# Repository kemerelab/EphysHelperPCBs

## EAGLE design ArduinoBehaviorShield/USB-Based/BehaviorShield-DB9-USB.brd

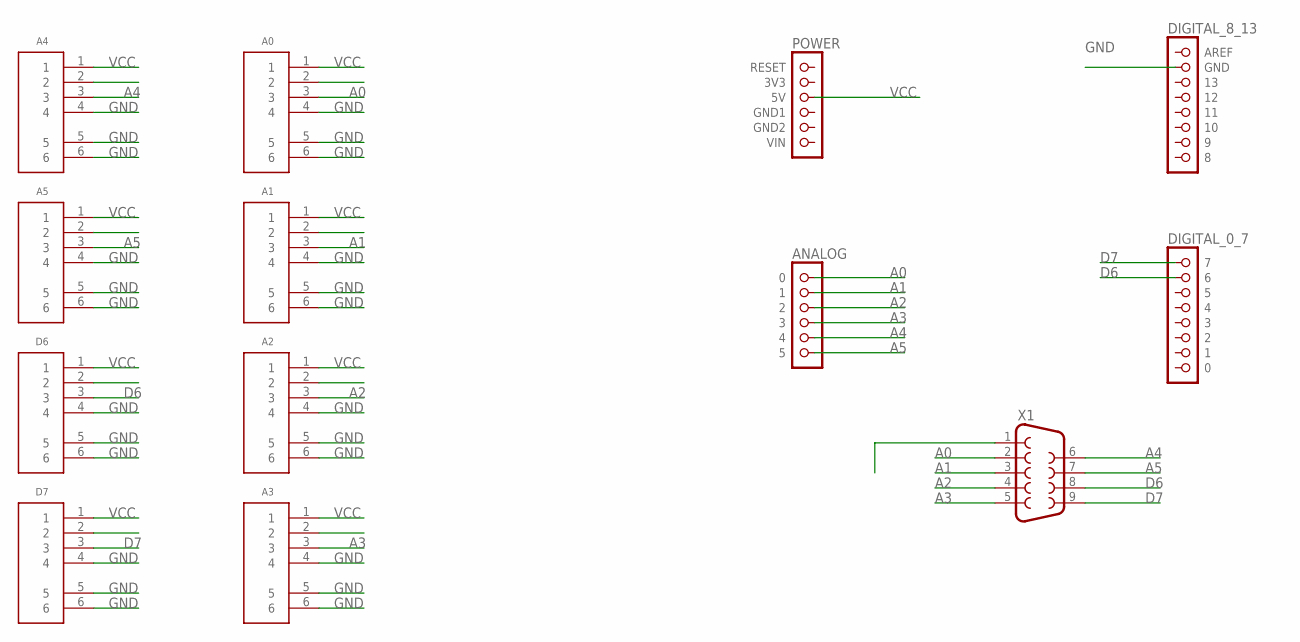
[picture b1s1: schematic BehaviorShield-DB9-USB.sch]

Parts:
A0, A1, A2, A3, A4, A5: USB-A-S-X-X-TH
D6, D7: USB-A-S-X-X-TH
U$1: POWER; 1X06
U$2: ANALOG; 1X06
U$3: DIGITAL_0_7; 1X08
U$4: DIGITAL_8_13; 1X08
X1: F09HP

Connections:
A0: A0.3, U$2.1 (0), X1.2
A1: A1.3, U$2.2 (1), X1.3
A2: A2.3, U$2.3 (2), X1.4
A3: A3.3, U$2.4 (3), X1.5
A4: A4.3, U$2.5 (4), X1.6
A5: A5.3, U$2.6 (5), X1.7
D6: D6.3, U$3.2 (6), X1.8
D7: D7.3, U$3.1 (7), X1.9
GND: A0.4, A0.5, A0.6, A1.4, A1.5, A1.6, A2.4, A2.5, A2.6, A3.4, A3.5, A3.6, A4.4, A4.5, A4.6, A5.4, A5.5, A5.6, D6.4, D6.5, D6.6, D7.4, D7.5, D7.6, U$4.2 (GND), X1.1
VCC: A0.1, A1.1, A2.1, A3.1, A4.1, A5.1, D6.1, D7.1, U$1.3 (5V)

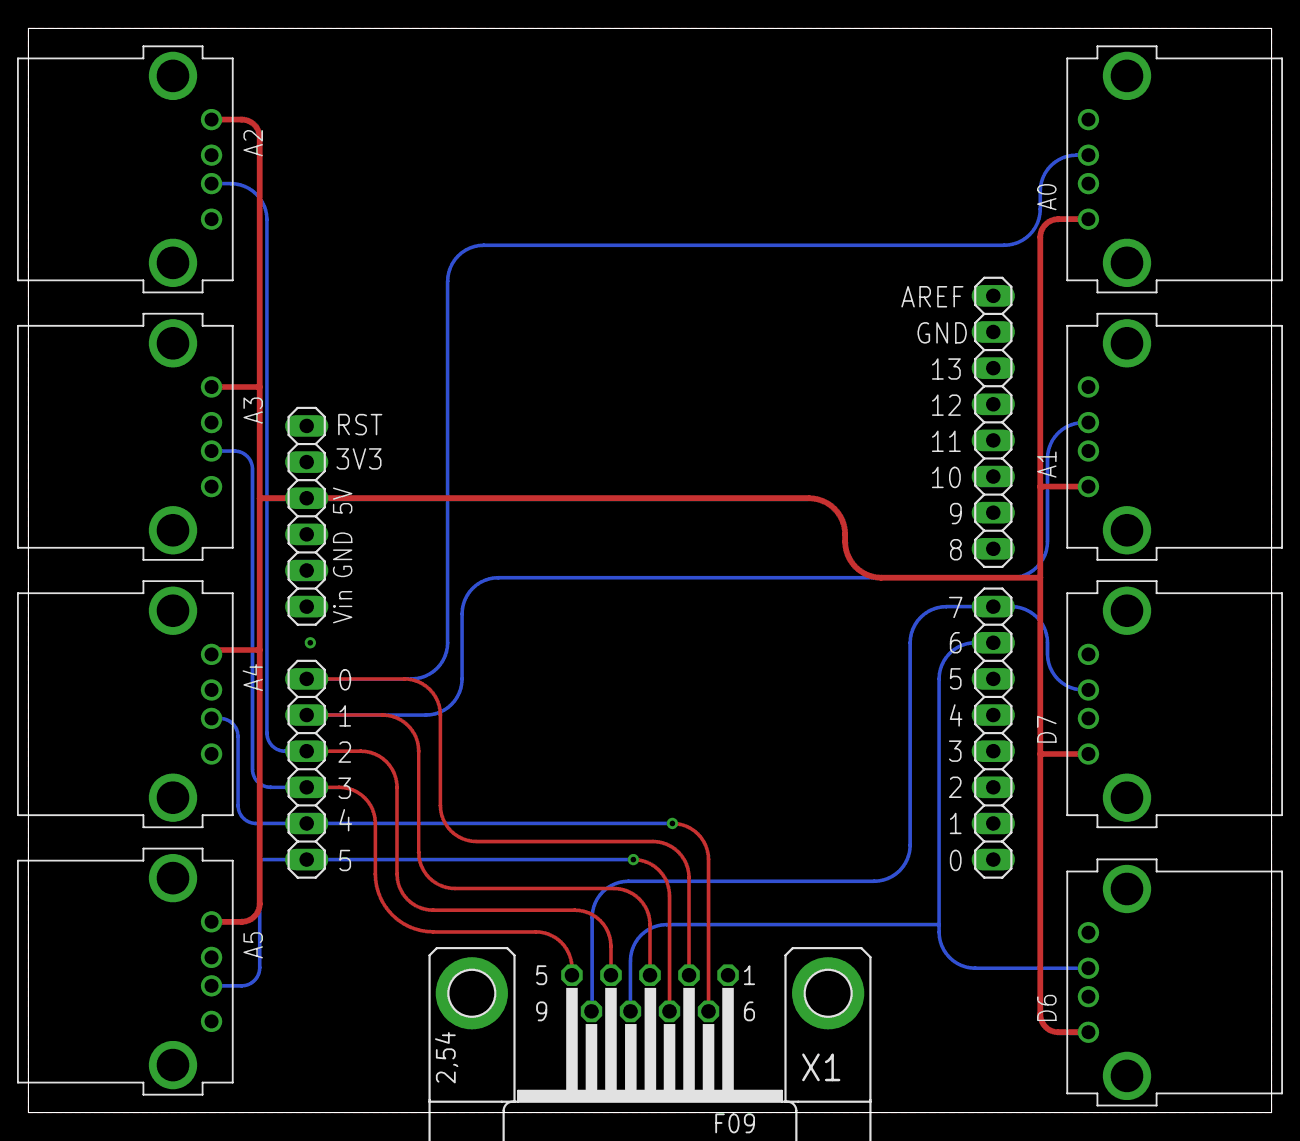
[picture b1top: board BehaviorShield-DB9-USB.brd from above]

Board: 2 copper layers, 87.4 x 76.2 mm, 13 parts (0 on the bottom side), 10 nets.

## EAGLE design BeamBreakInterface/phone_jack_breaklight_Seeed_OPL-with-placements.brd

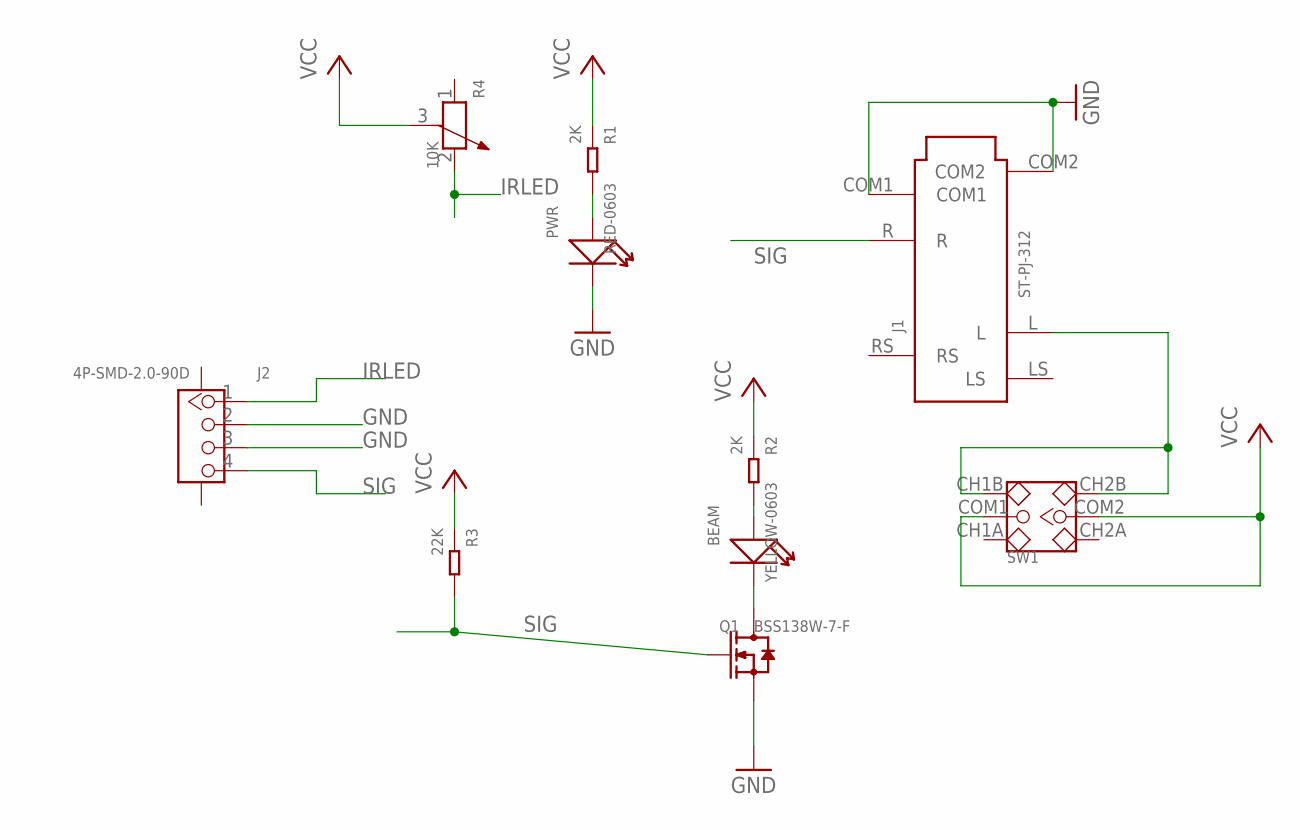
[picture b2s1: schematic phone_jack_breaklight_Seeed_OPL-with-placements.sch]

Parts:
J1: ST-PJ-312; AUDIO6P-SMD-3.5-14.0X6.4X5.0MM
J2: 4P-SMD-2.0-90D; HW4-SMD-2.0-90D
Q1: BSS138W-7-F; SOT-23
R1, R2: 2K; R0603
R3: 22K; R0603
R4: 10K; ADJR3-9.5X9.5X10.5MM
RED-0603: PWR; LED-0603
SW1: DIP-TOGGLE-SWITCH-2CH-(2X3P-2.54-90D)'90D'; SW6-2.54-9.0X3.5X3.2MM-90D
YELLOW-0603: BEAM; LED-0603

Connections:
GND: J1.COM1, J1.COM2, J2.2, J2.3, Q1.2 (S), RED-0603.-
IRLED: J2.1, R4.2
unnamed: R2.2, YELLOW-0603.+
unnamed: J1.L, SW1.CH1B, SW1.CH2B
unnamed: Q1.3 (D), YELLOW-0603.-
unnamed: R1.2, RED-0603.+
SIG: J1.R, J2.4, Q1.1 (G), R3.2
VCC: R1.1, R2.1, R3.1, R4.3, SW1.COM1, SW1.COM2

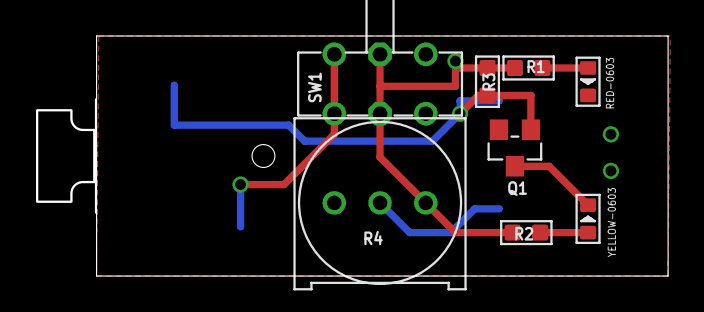
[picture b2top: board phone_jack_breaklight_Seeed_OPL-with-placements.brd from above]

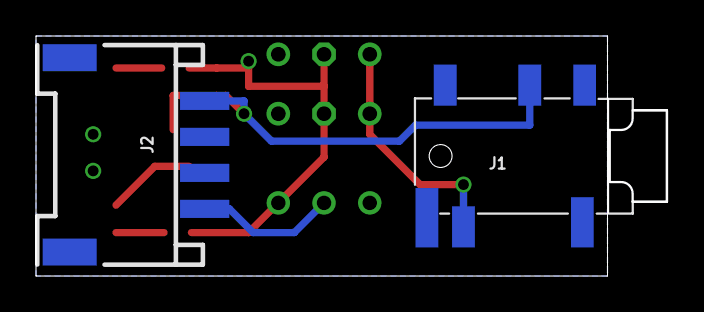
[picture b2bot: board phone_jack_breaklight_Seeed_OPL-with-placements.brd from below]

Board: 2 copper layers, 31.8 x 13.3 mm, 10 parts (2 on the bottom side), 8 nets.

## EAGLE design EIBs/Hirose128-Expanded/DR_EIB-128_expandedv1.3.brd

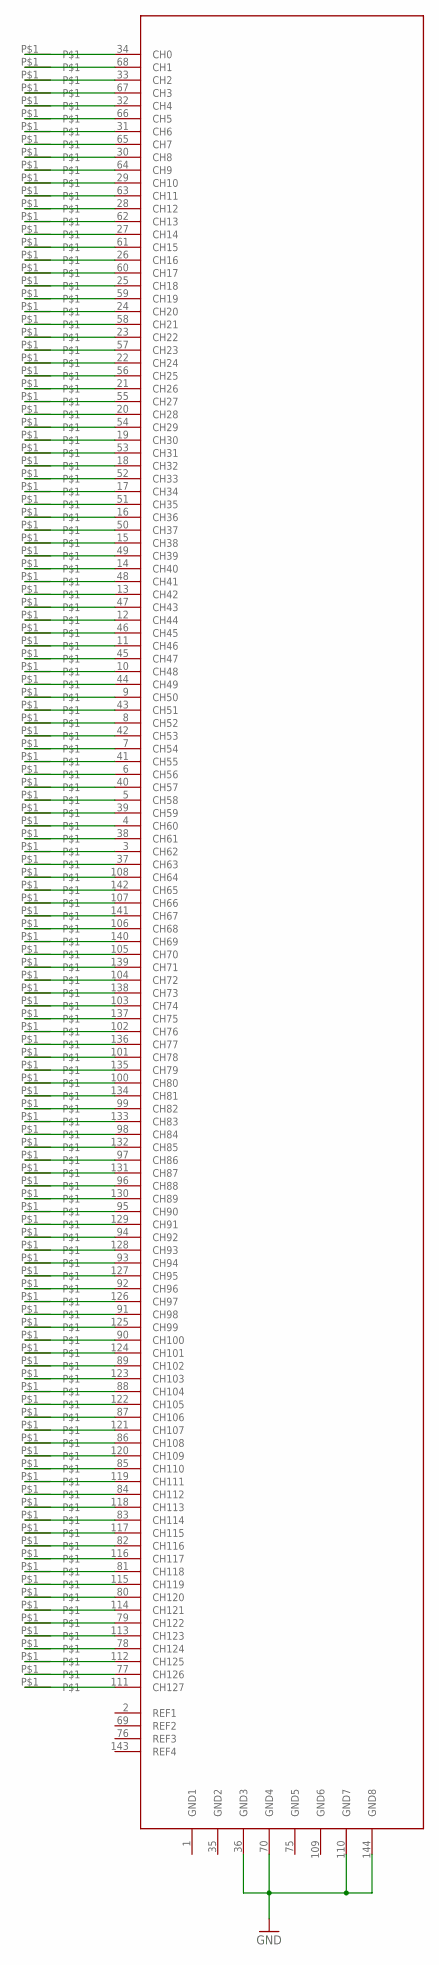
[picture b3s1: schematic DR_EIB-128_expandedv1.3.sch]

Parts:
H$0, H$1, H$2, H$3, H$4, H$5, H$6, H$7, H$8, H$9, H$10, H$11, H$12, H$13, H$14, H$15, H$16, H$17, H$18, H$19, H$20, H$21, H$22, H$23, H$24, H$25, H$26, H$27, H$28, H$29, H$30, H$31, H$32, H$33, H$34, H$35, H$36, H$37, H$38, H$39, H$40, H$41, H$42, H$43, H$44, H$45, H$46, H$47, H$48, H$49, H$50, H$51, H$52, H$53, H$54, H$55, H$56, H$57, H$58, H$59, H$60, H$61, H$62, H$63, H$64, H$65, H$66, H$67, H$68, H$69, H$70, H$71, H$72, H$73, H$74, H$75, H$76, H$77, H$78, H$79, H$80, H$81, H$82, H$83, H$84, H$85, H$86, H$87, H$88, H$89, H$90, H$91, H$92, H$93, H$94, H$95, H$96, H$97, H$98, H$99, H$100, H$101, H$102, H$103, H$104, H$105, H$106, H$107, H$108, H$109, H$110, H$111, H$112, H$113, H$114, H$115, H$116, H$117, H$118, H$119, H$120, H$121, H$122, H$123, H$124, H$125, H$126, H$127: TARRAYSHUTTLEHOLE
U$3: 128CH-MODULE

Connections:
GND: U$3.36 (GND3), U$3.70 (GND4), U$3.110 (GND7), U$3.144 (GND8)
GND1: U$3.1 (GND1)
GND2: U$3.35 (GND2)
GND5: U$3.75 (GND5)
GND6: U$3.109 (GND6)
unnamed: H$0.P$1, U$3.34 (CH0)
unnamed: H$1.P$1, U$3.68 (CH1)
unnamed: H$2.P$1, U$3.33 (CH2)
unnamed: H$3.P$1, U$3.67 (CH3)
unnamed: H$4.P$1, U$3.32 (CH4)
unnamed: H$5.P$1, U$3.66 (CH5)
unnamed: H$6.P$1, U$3.31 (CH6)
unnamed: H$7.P$1, U$3.65 (CH7)
unnamed: H$8.P$1, U$3.30 (CH8)
unnamed: H$9.P$1, U$3.64 (CH9)
unnamed: H$10.P$1, U$3.29 (CH10)
unnamed: H$11.P$1, U$3.63 (CH11)
unnamed: H$12.P$1, U$3.28 (CH12)
unnamed: H$13.P$1, U$3.62 (CH13)
unnamed: H$14.P$1, U$3.27 (CH14)
unnamed: H$15.P$1, U$3.61 (CH15)
unnamed: H$16.P$1, U$3.26 (CH16)
unnamed: H$17.P$1, U$3.60 (CH17)
unnamed: H$18.P$1, U$3.25 (CH18)
unnamed: H$19.P$1, U$3.59 (CH19)
unnamed: H$20.P$1, U$3.24 (CH20)
unnamed: H$21.P$1, U$3.58 (CH21)
unnamed: H$22.P$1, U$3.23 (CH22)
unnamed: H$23.P$1, U$3.57 (CH23)
unnamed: H$24.P$1, U$3.22 (CH24)
unnamed: H$25.P$1, U$3.56 (CH25)
unnamed: H$26.P$1, U$3.21 (CH26)
unnamed: H$27.P$1, U$3.55 (CH27)
unnamed: H$28.P$1, U$3.20 (CH28)
unnamed: H$29.P$1, U$3.54 (CH29)
unnamed: H$30.P$1, U$3.19 (CH30)
unnamed: H$31.P$1, U$3.53 (CH31)
unnamed: H$33.P$1, U$3.52 (CH33)
unnamed: H$35.P$1, U$3.51 (CH35)
unnamed: H$37.P$1, U$3.50 (CH37)
unnamed: H$39.P$1, U$3.49 (CH39)
unnamed: H$41.P$1, U$3.48 (CH41)
unnamed: H$43.P$1, U$3.47 (CH43)
unnamed: H$45.P$1, U$3.46 (CH45)
unnamed: H$47.P$1, U$3.45 (CH47)
unnamed: H$49.P$1, U$3.44 (CH49)
unnamed: H$51.P$1, U$3.43 (CH51)
unnamed: H$53.P$1, U$3.42 (CH53)
unnamed: H$55.P$1, U$3.41 (CH55)
unnamed: H$57.P$1, U$3.40 (CH57)
unnamed: H$59.P$1, U$3.39 (CH59)
unnamed: H$61.P$1, U$3.38 (CH61)
unnamed: H$63.P$1, U$3.37 (CH63)
unnamed: H$96.P$1, U$3.92 (CH96)
unnamed: H$98.P$1, U$3.91 (CH98)
unnamed: H$100.P$1, U$3.90 (CH100)
unnamed: H$102.P$1, U$3.89 (CH102)
unnamed: H$104.P$1, U$3.88 (CH104)
unnamed: H$106.P$1, U$3.87 (CH106)
unnamed: H$108.P$1, U$3.86 (CH108)
unnamed: H$110.P$1, U$3.85 (CH110)
unnamed: H$112.P$1, U$3.84 (CH112)
unnamed: H$114.P$1, U$3.83 (CH114)
unnamed: H$116.P$1, U$3.82 (CH116)
unnamed: H$118.P$1, U$3.81 (CH118)
T2_1: H$56.P$1, U$3.6 (CH56)
T2_2: H$58.P$1, U$3.5 (CH58)
T2_3: H$60.P$1, U$3.4 (CH60)
T2_4: H$62.P$1, U$3.3 (CH62)
T3_1: H$54.P$1, U$3.7 (CH54)
T3_2: H$52.P$1, U$3.8 (CH52)
T3_3: H$50.P$1, U$3.9 (CH50)
T3_4: H$48.P$1, U$3.10 (CH48)
T4_1: H$46.P$1, U$3.11 (CH46)
T4_2: H$44.P$1, U$3.12 (CH44)
T4_3: H$42.P$1, U$3.13 (CH42)
T4_4: H$40.P$1, U$3.14 (CH40)
T5_1: H$38.P$1, U$3.15 (CH38)
T5_2: H$36.P$1, U$3.16 (CH36)
T5_3: H$34.P$1, U$3.17 (CH34)
T5_4: H$32.P$1, U$3.18 (CH32)
T6_1: H$94.P$1, U$3.93 (CH94)
T6_2: H$92.P$1, U$3.94 (CH92)
T6_3: H$90.P$1, U$3.95 (CH90)
T6_4: H$88.P$1, U$3.96 (CH88)
T7_1: H$86.P$1, U$3.97 (CH86)
T7_2: H$84.P$1, U$3.98 (CH84)
T7_3: H$82.P$1, U$3.99 (CH82)
T7_4: H$80.P$1, U$3.100 (CH80)
T8_1: H$78.P$1, U$3.101 (CH78)
T8_2: H$76.P$1, U$3.102 (CH76)
T8_3: H$74.P$1, U$3.103 (CH74)
T8_4: H$72.P$1, U$3.104 (CH72)
T9_1: H$64.P$1, U$3.108 (CH64)
T9_2: H$66.P$1, U$3.107 (CH66)
T9_3: H$68.P$1, U$3.106 (CH68)
T9_4: H$70.P$1, U$3.105 (CH70)
T10_1: H$71.P$1, U$3.139 (CH71)
T10_2: H$69.P$1, U$3.140 (CH69)
T10_3: H$67.P$1, U$3.141 (CH67)
T10_4: H$65.P$1, U$3.142 (CH65)
T11_1: H$127.P$1, U$3.111 (CH127)
T11_2: H$125.P$1, U$3.112 (CH125)
T11_3: H$123.P$1, U$3.113 (CH123)
T11_4: H$121.P$1, U$3.114 (CH121)
T12_1: H$120.P$1, U$3.80 (CH120)
T12_2: H$122.P$1, U$3.79 (CH122)
T12_3: H$124.P$1, U$3.78 (CH124)
T12_4: H$126.P$1, U$3.77 (CH126)
T21_1: H$73.P$1, U$3.138 (CH73)
T21_2: H$75.P$1, U$3.137 (CH75)
T21_3: H$77.P$1, U$3.136 (CH77)
T21_4: H$79.P$1, U$3.135 (CH79)
T22_1: H$81.P$1, U$3.134 (CH81)
T22_2: H$83.P$1, U$3.133 (CH83)
T22_3: H$85.P$1, U$3.132 (CH85)
T22_4: H$87.P$1, U$3.131 (CH87)
T23_1: H$89.P$1, U$3.130 (CH89)
T23_2: H$91.P$1, U$3.129 (CH91)
T23_3: H$93.P$1, U$3.128 (CH93)
T23_4: H$95.P$1, U$3.127 (CH95)
T24_1: H$97.P$1, U$3.126 (CH97)
T24_2: H$99.P$1, U$3.125 (CH99)
T24_3: H$101.P$1, U$3.124 (CH101)
T24_4: H$103.P$1, U$3.123 (CH103)
T25_1: H$105.P$1, U$3.122 (CH105)
T25_2: H$107.P$1, U$3.121 (CH107)
T25_3: H$109.P$1, U$3.120 (CH109)
T25_4: H$111.P$1, U$3.119 (CH111)
T26_1: H$113.P$1, U$3.118 (CH113)
T26_2: H$115.P$1, U$3.117 (CH115)
T26_3: H$117.P$1, U$3.116 (CH117)
T26_4: H$119.P$1, U$3.115 (CH119)

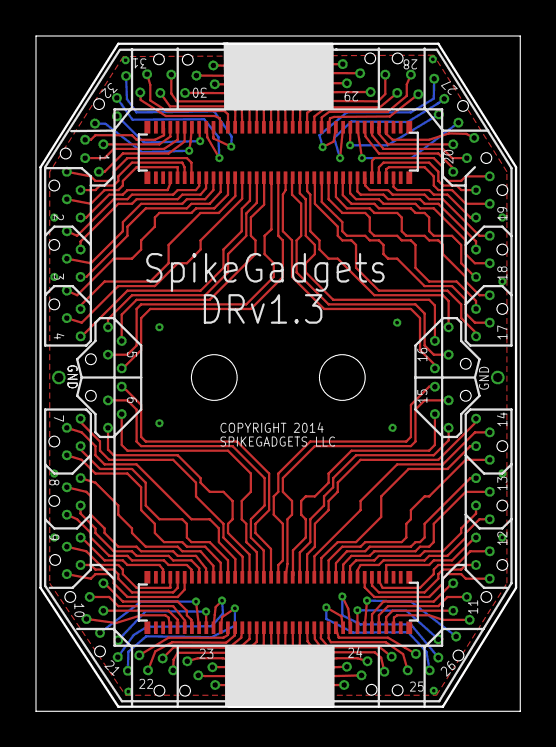
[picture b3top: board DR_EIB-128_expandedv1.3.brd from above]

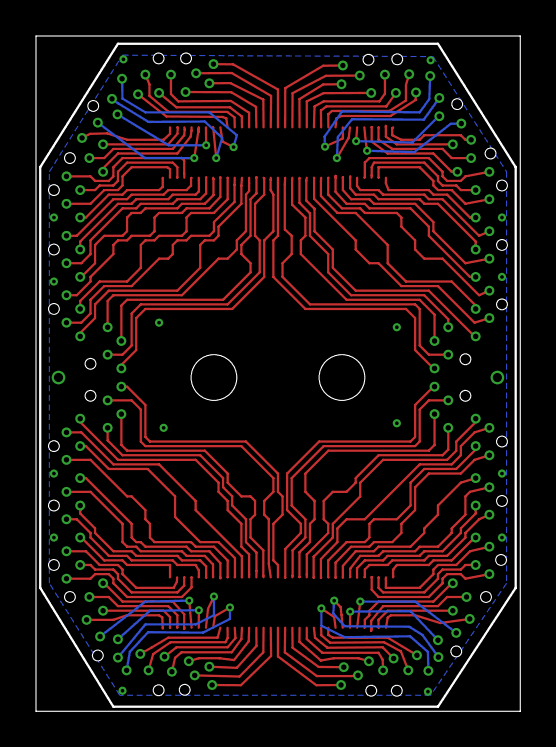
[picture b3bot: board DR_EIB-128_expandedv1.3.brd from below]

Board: 2 copper layers, 26.9 x 37.5 mm, 129 parts (59 on the bottom side), 129 nets.

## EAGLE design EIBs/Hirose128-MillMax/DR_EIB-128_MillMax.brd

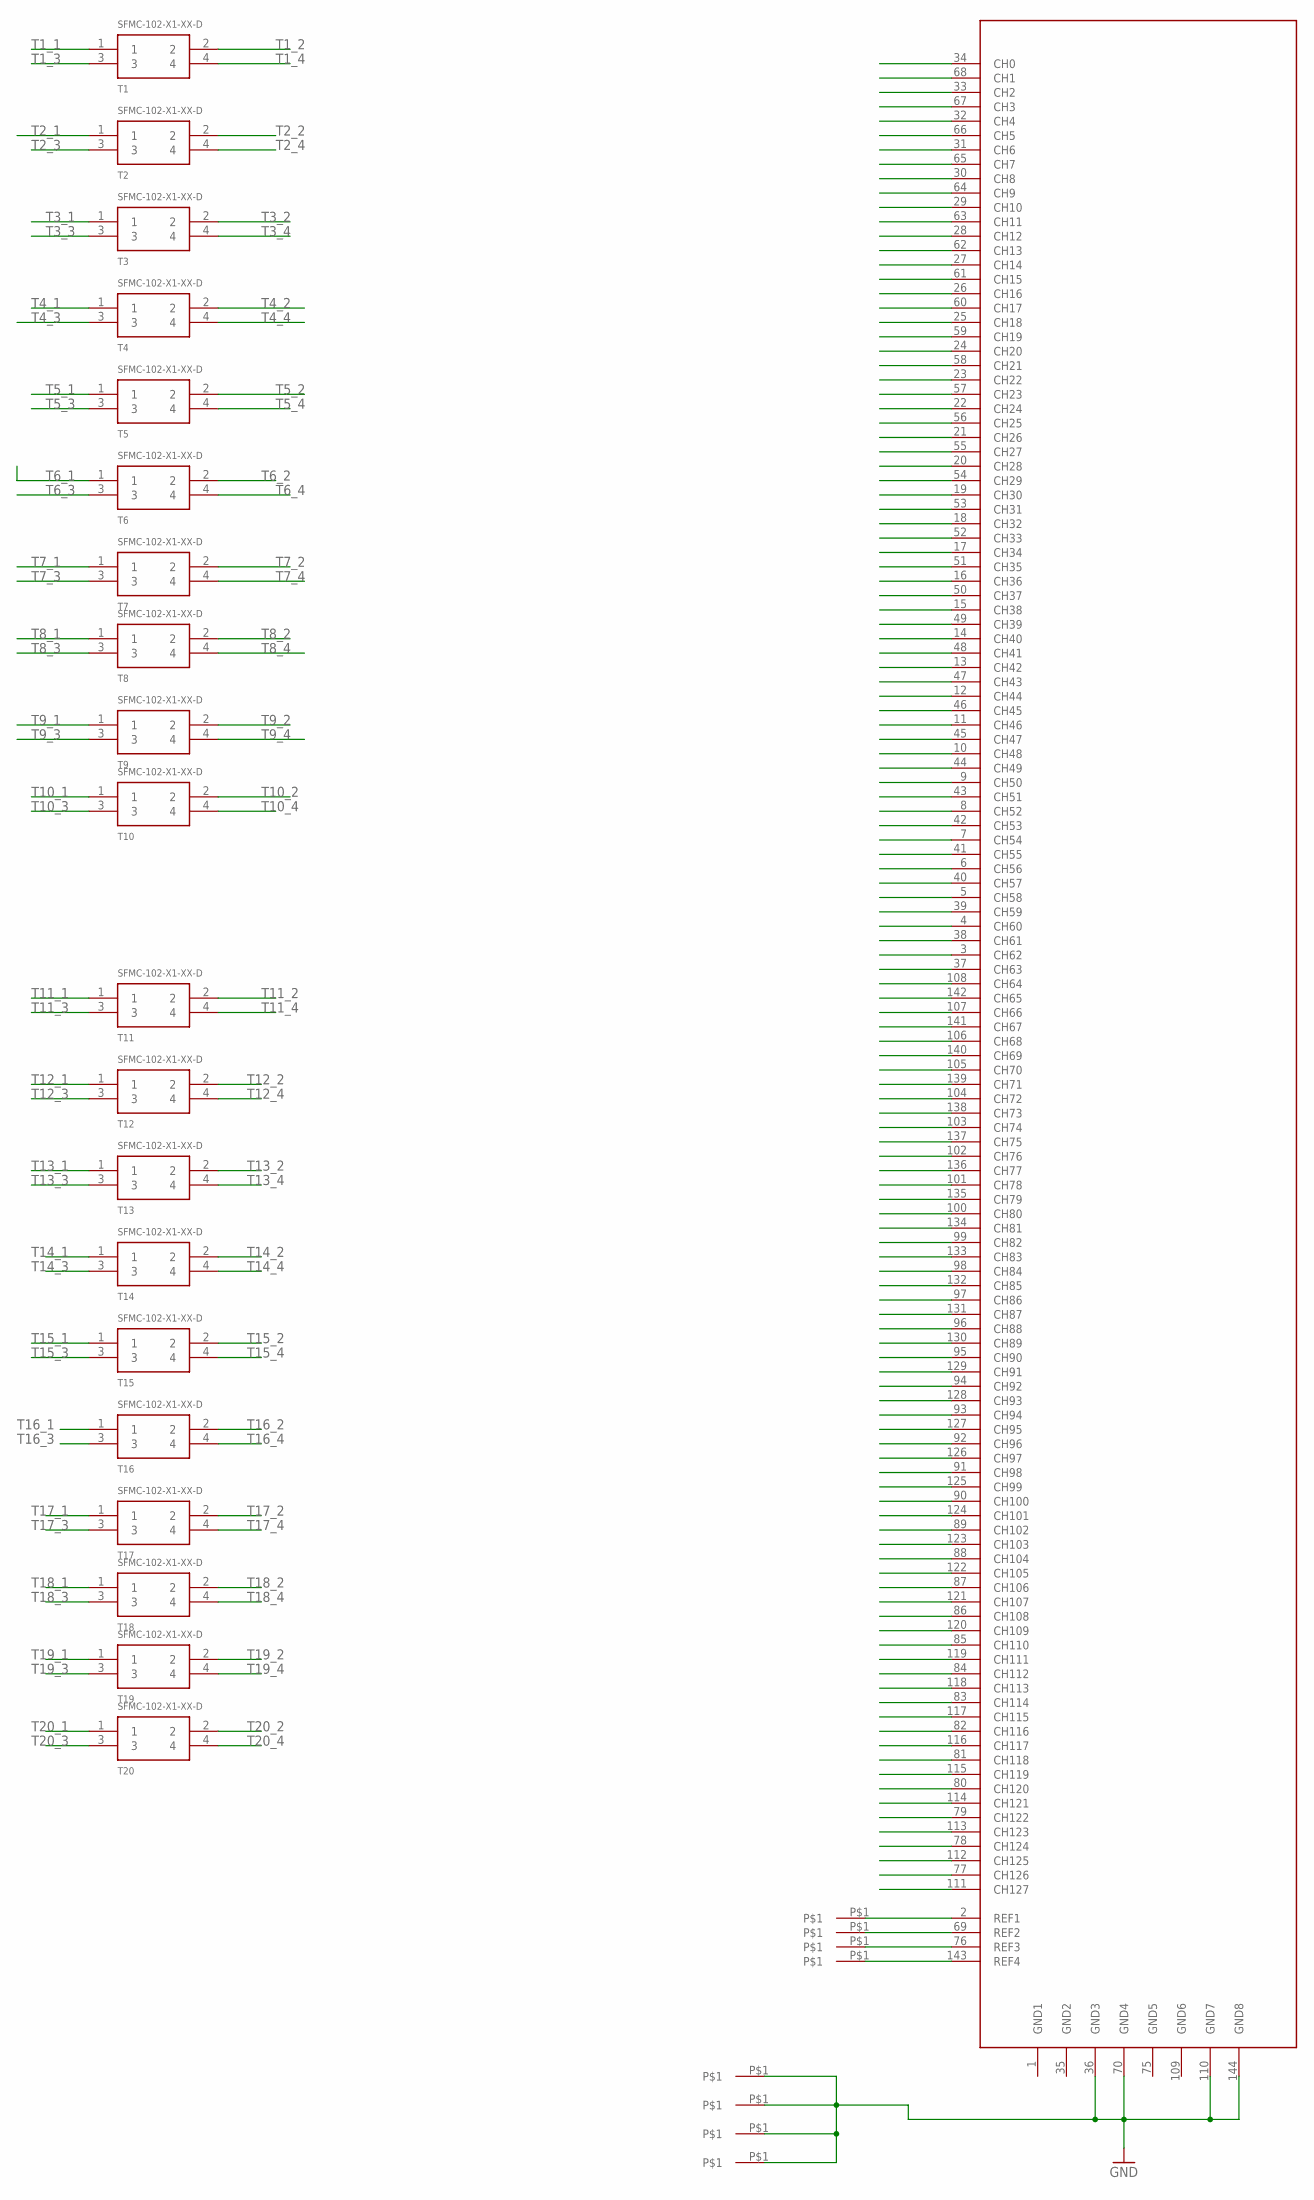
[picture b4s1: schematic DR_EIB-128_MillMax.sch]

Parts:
T1, T2, T3, T4, T5, T6, T7, T8, T9, T10, T11, T12, T13, T14, T15, T16, T17, T18, T19, T20: SFMC-102-X1-XX-D
U$1, U$2, U$4, U$5, U$6, U$7, U$8, U$9: TARRAYSHUTTLEHOLE
U$3: 128CH-MODULE

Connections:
GND: U$1.P$1, U$2.P$1, U$3.36 (GND3), U$3.70 (GND4), U$3.110 (GND7), U$3.144 (GND8), U$4.P$1, U$5.P$1
GND1: U$3.1 (GND1)
GND2: U$3.35 (GND2)
GND5: U$3.75 (GND5)
GND6: U$3.109 (GND6)
unnamed: U$3.2 (REF1), U$6.P$1
unnamed: U$3.69 (REF2), U$7.P$1
unnamed: U$3.76 (REF3), U$8.P$1
unnamed: U$3.143 (REF4), U$9.P$1
T1_1: T1.1, U$3.37 (CH63)
T1_2: T1.2, U$3.38 (CH61)
T1_3: T1.3, U$3.39 (CH59)
T1_4: T1.4, U$3.40 (CH57)
T2_1: T2.1, U$3.6 (CH56)
T2_2: T2.2, U$3.5 (CH58)
T2_3: T2.3, U$3.4 (CH60)
T2_4: T2.4, U$3.3 (CH62)
T3_1: T3.1, U$3.7 (CH54)
T3_2: T3.2, U$3.8 (CH52)
T3_3: T3.3, U$3.9 (CH50)
T3_4: T3.4, U$3.10 (CH48)
T4_1: T4.1, U$3.11 (CH46)
T4_2: T4.2, U$3.12 (CH44)
T4_3: T4.3, U$3.13 (CH42)
T4_4: T4.4, U$3.14 (CH40)
T5_1: T5.1, U$3.15 (CH38)
T5_2: T5.2, U$3.16 (CH36)
T5_3: T5.3, U$3.17 (CH34)
T5_4: T5.4, U$3.18 (CH32)
T6_1: T6.1, U$3.93 (CH94)
T6_2: T6.2, U$3.94 (CH92)
T6_3: T6.3, U$3.95 (CH90)
T6_4: T6.4, U$3.96 (CH88)
T7_1: T7.1, U$3.97 (CH86)
T7_2: T7.2, U$3.98 (CH84)
T7_3: T7.3, U$3.99 (CH82)
T7_4: T7.4, U$3.100 (CH80)
T8_1: T8.1, U$3.101 (CH78)
T8_2: T8.2, U$3.102 (CH76)
T8_3: T8.3, U$3.103 (CH74)
T8_4: T8.4, U$3.104 (CH72)
T9_1: T9.1, U$3.108 (CH64)
T9_2: T9.2, U$3.107 (CH66)
T9_3: T9.3, U$3.106 (CH68)
T9_4: T9.4, U$3.105 (CH70)
T10_1: T10.1, U$3.139 (CH71)
T10_2: T10.2, U$3.140 (CH69)
T10_3: T10.3, U$3.141 (CH67)
T10_4: T10.4, U$3.142 (CH65)
T11_1: T11.1, U$3.111 (CH127)
T11_2: T11.2, U$3.112 (CH125)
T11_3: T11.3, U$3.113 (CH123)
T11_4: T11.4, U$3.114 (CH121)
T12_1: T12.1, U$3.80 (CH120)
T12_2: T12.2, U$3.79 (CH122)
T12_3: T12.3, U$3.78 (CH124)
T12_4: T12.4, U$3.77 (CH126)
T13_1: T13.1, U$3.81 (CH118)
T13_2: T13.2, U$3.82 (CH116)
T13_3: T13.3, U$3.83 (CH114)
T13_4: T13.4, U$3.84 (CH112)
T14_1: T14.1, U$3.85 (CH110)
T14_2: T14.2, U$3.86 (CH108)
T14_3: T14.3, U$3.87 (CH106)
T14_4: T14.4, U$3.88 (CH104)
T15_1: T15.1, U$3.89 (CH102)
T15_2: T15.2, U$3.90 (CH100)
T15_3: T15.3, U$3.91 (CH98)
T15_4: T15.4, U$3.92 (CH96)
T16_1: T16.1, U$3.19 (CH30)
T16_2: T16.2, U$3.20 (CH28)
T16_3: T16.3, U$3.21 (CH26)
T16_4: T16.4, U$3.22 (CH24)
T17_1: T17.1, U$3.23 (CH22)
T17_2: T17.2, U$3.24 (CH20)
T17_3: T17.3, U$3.25 (CH18)
T17_4: T17.4, U$3.26 (CH16)
T18_1: T18.1, U$3.27 (CH14)
T18_2: T18.2, U$3.28 (CH12)
T18_3: T18.3, U$3.29 (CH10)
T18_4: T18.4, U$3.30 (CH8)
T19_1: T19.1, U$3.34 (CH0)
T19_2: T19.2, U$3.33 (CH2)
T19_3: T19.3, U$3.32 (CH4)
T19_4: T19.4, U$3.31 (CH6)
T20_1: T20.1, U$3.65 (CH7)
T20_2: T20.2, U$3.66 (CH5)
T20_3: T20.3, U$3.67 (CH3)
T20_4: T20.4, U$3.68 (CH1)
T21_1: U$3.138 (CH73)
T21_2: U$3.137 (CH75)
T21_3: U$3.136 (CH77)
T21_4: U$3.135 (CH79)
T22_1: U$3.134 (CH81)
T22_2: U$3.133 (CH83)
T22_3: U$3.132 (CH85)
T22_4: U$3.131 (CH87)
T23_1: U$3.130 (CH89)
T23_2: U$3.129 (CH91)
T23_3: U$3.128 (CH93)
T23_4: U$3.127 (CH95)
T24_1: U$3.126 (CH97)
T24_2: U$3.125 (CH99)
T24_3: U$3.124 (CH101)
T24_4: U$3.123 (CH103)
T25_1: U$3.122 (CH105)
T25_2: U$3.121 (CH107)
T25_3: U$3.120 (CH109)
T25_4: U$3.119 (CH111)
T26_1: U$3.118 (CH113)
T26_2: U$3.117 (CH115)
T26_3: U$3.116 (CH117)
T26_4: U$3.115 (CH119)
T27_1: U$3.64 (CH9)
T27_2: U$3.63 (CH11)
T27_3: U$3.62 (CH13)
T27_4: U$3.61 (CH15)
T28_1: U$3.60 (CH17)
T28_2: U$3.59 (CH19)
T28_3: U$3.58 (CH21)
T28_4: U$3.57 (CH23)
T29_1: U$3.56 (CH25)
T29_2: U$3.55 (CH27)
T29_3: U$3.54 (CH29)
T29_4: U$3.53 (CH31)
T30_1: U$3.52 (CH33)
T30_2: U$3.51 (CH35)
T30_3: U$3.50 (CH37)
T30_4: U$3.49 (CH39)
T31_1: U$3.48 (CH41)
T31_2: U$3.47 (CH43)
T31_3: U$3.46 (CH45)
T31_4: U$3.45 (CH47)
T32_1: U$3.44 (CH49)
T32_2: U$3.43 (CH51)
T32_3: U$3.42 (CH53)
T32_4: U$3.41 (CH55)

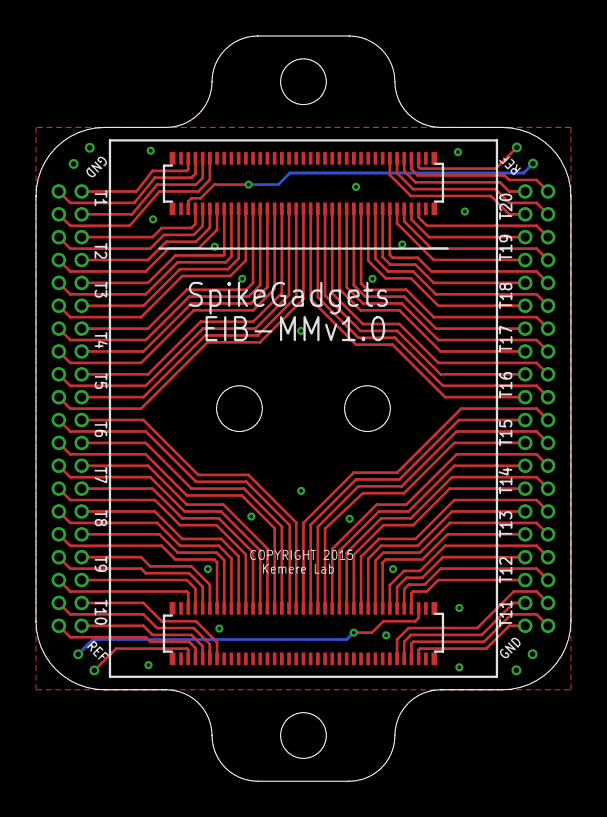
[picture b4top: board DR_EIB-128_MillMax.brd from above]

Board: 2 copper layers, 29.7 x 41.4 mm, 29 parts (0 on the bottom side), 85 nets.

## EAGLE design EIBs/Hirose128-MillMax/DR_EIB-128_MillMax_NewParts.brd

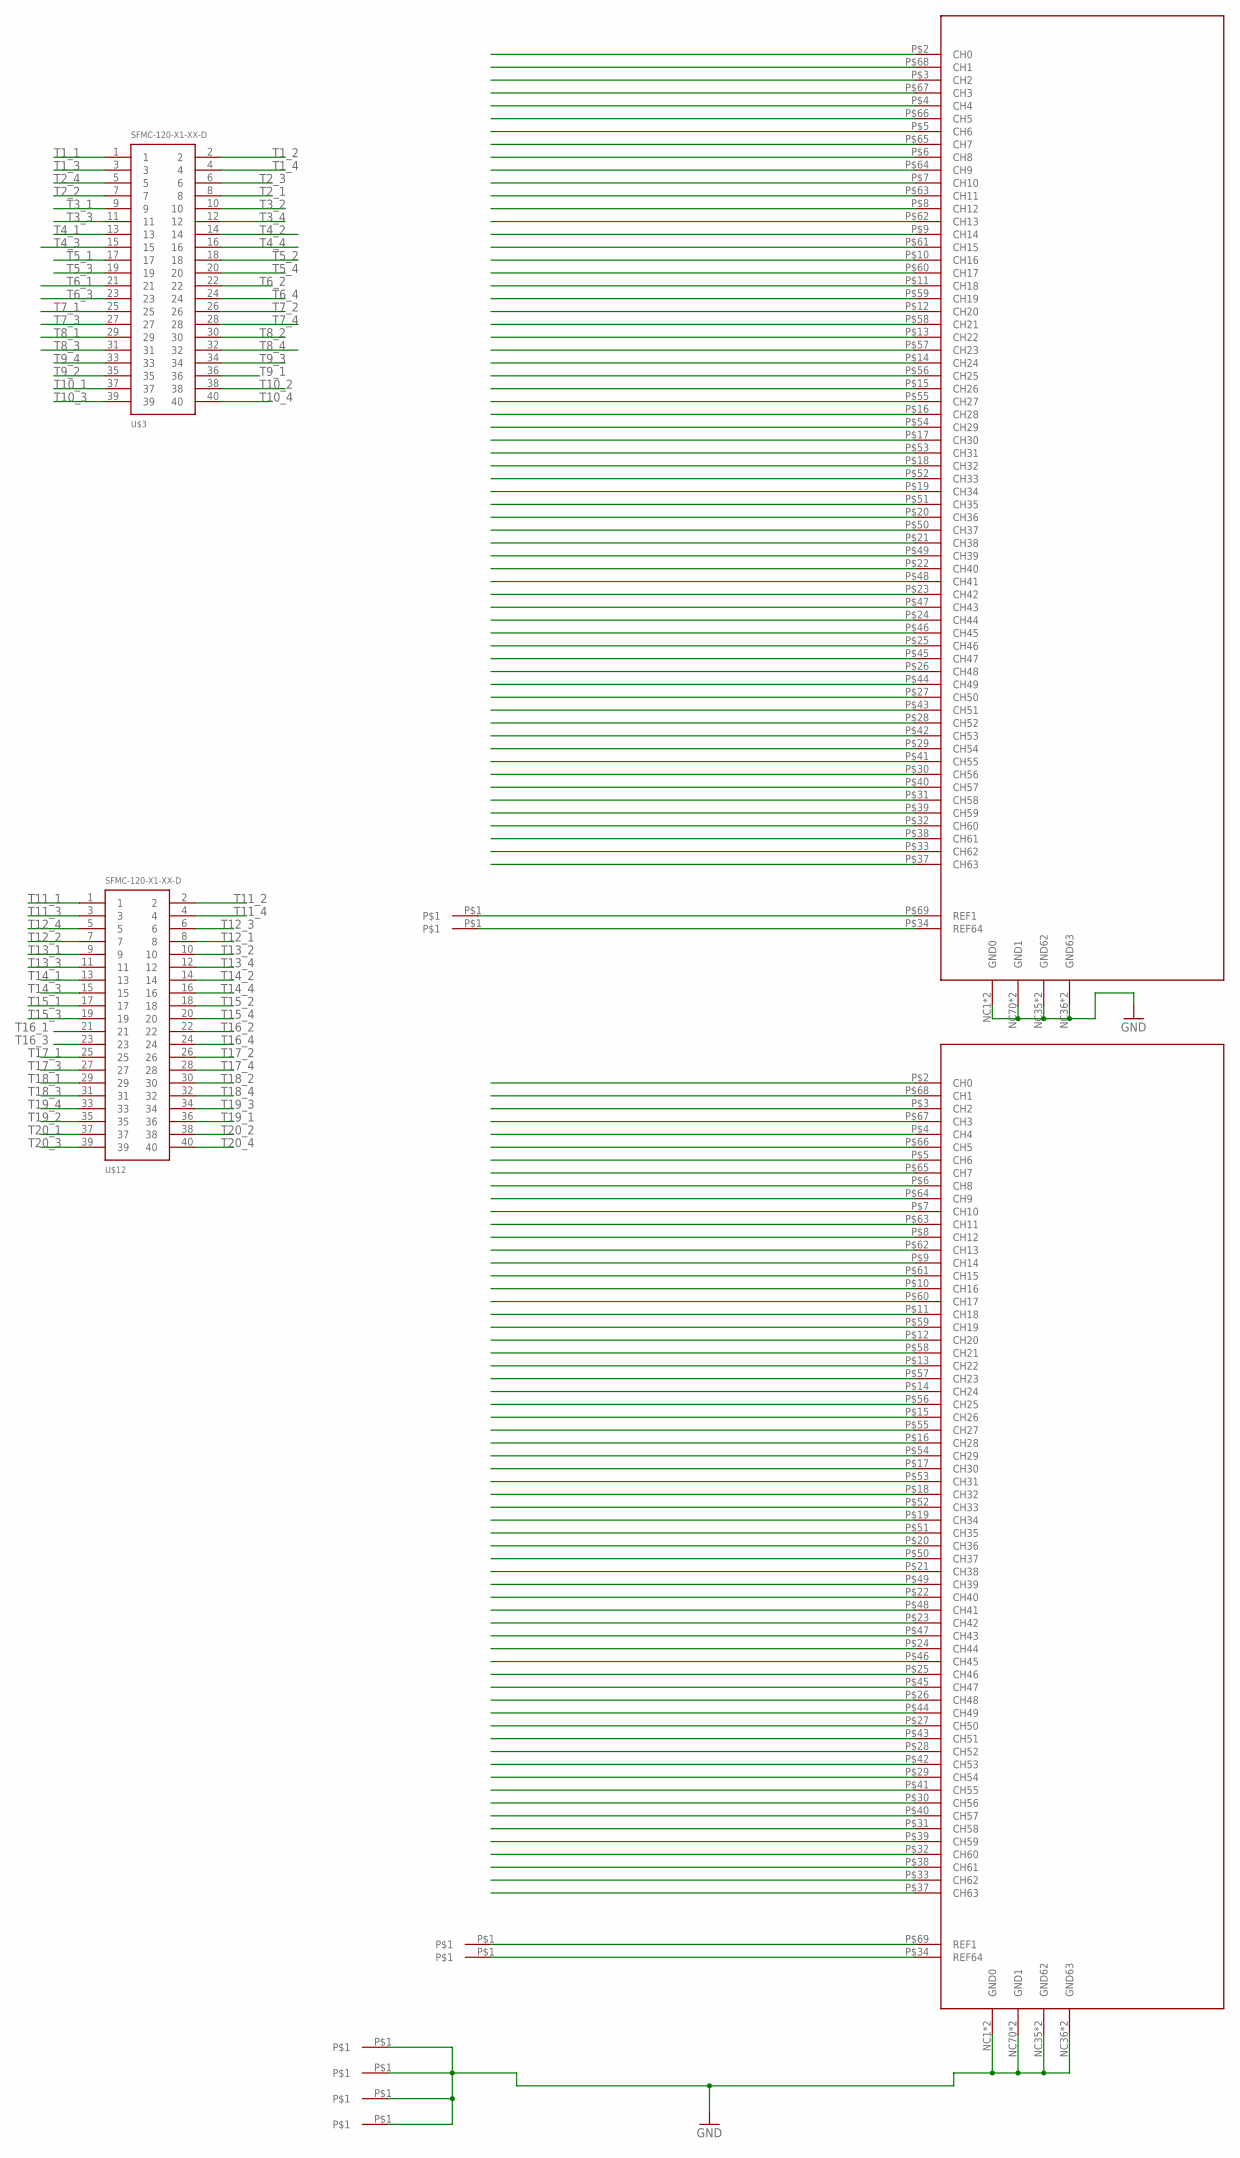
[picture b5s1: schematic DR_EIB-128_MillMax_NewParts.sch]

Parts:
U$1, U$2, U$4, U$5, U$6, U$7, U$8, U$9: TARRAYSHUTTLEHOLE
U$3, U$12: SFMC-120-X1-XX-D
U$10, U$11: HIROSE-70PIN-HEADER; DF40C-70DP-0.4V

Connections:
GND: U$1.P$1, U$2.P$1, U$4.P$1, U$5.P$1, U$10.NC1 (GND0), U$10.NC35 (GND62), U$10.NC36 (GND63), U$10.NC70 (GND1), U$10.P$1 (GND0), U$10.P$35 (GND62), U$10.P$36 (GND63), U$10.P$70 (GND1), U$11.NC1 (GND0), U$11.NC35 (GND62), U$11.NC36 (GND63), U$11.NC70 (GND1), U$11.P$1 (GND0), U$11.P$35 (GND62), U$11.P$36 (GND63), U$11.P$70 (GND1)
unnamed: U$9.P$1, U$11.P$69 (REF1)
unnamed: U$8.P$1, U$11.P$34 (REF64)
unnamed: U$6.P$1, U$10.P$34 (REF64)
unnamed: U$7.P$1, U$10.P$69 (REF1)
T1_1: U$3.1, U$10.P$37 (CH63)
T1_2: U$3.2, U$10.P$38 (CH61)
T1_3: U$3.3, U$10.P$39 (CH59)
T1_4: U$3.4, U$10.P$40 (CH57)
T2_1: U$3.8, U$10.P$30 (CH56)
T2_2: U$3.7, U$10.P$31 (CH58)
T2_3: U$3.6, U$10.P$32 (CH60)
T2_4: U$3.5, U$10.P$33 (CH62)
T3_1: U$3.9, U$10.P$29 (CH54)
T3_2: U$3.10, U$10.P$28 (CH52)
T3_3: U$3.11, U$10.P$27 (CH50)
T3_4: U$3.12, U$10.P$26 (CH48)
T4_1: U$3.13, U$10.P$25 (CH46)
T4_2: U$3.14, U$10.P$24 (CH44)
T4_3: U$3.15, U$10.P$23 (CH42)
T4_4: U$3.16, U$10.P$22 (CH40)
T5_1: U$3.17, U$10.P$21 (CH38)
T5_2: U$3.18, U$10.P$20 (CH36)
T5_3: U$3.19, U$10.P$19 (CH34)
T5_4: U$3.20, U$10.P$18 (CH32)
T6_1: U$3.21, U$11.P$17 (CH30)
T6_2: U$3.22, U$11.P$16 (CH28)
T6_3: U$3.23, U$11.P$15 (CH26)
T6_4: U$3.24, U$11.P$14 (CH24)
T7_1: U$3.25, U$11.P$13 (CH22)
T7_2: U$3.26, U$11.P$12 (CH20)
T7_3: U$3.27, U$11.P$11 (CH18)
T7_4: U$3.28, U$11.P$10 (CH16)
T8_1: U$3.29, U$11.P$9 (CH14)
T8_2: U$3.30, U$11.P$8 (CH12)
T8_3: U$3.31, U$11.P$7 (CH10)
T8_4: U$3.32, U$11.P$6 (CH8)
T9_1: U$3.36, U$11.P$2 (CH0)
T9_2: U$3.35, U$11.P$3 (CH2)
T9_3: U$3.34, U$11.P$4 (CH4)
T9_4: U$3.33, U$11.P$5 (CH6)
T10_1: U$3.37, U$11.P$65 (CH7)
T10_2: U$3.38, U$11.P$66 (CH5)
T10_3: U$3.39, U$11.P$67 (CH3)
T10_4: U$3.40, U$11.P$68 (CH1)
T11_1: U$11.P$37 (CH63), U$12.1
T11_2: U$11.P$38 (CH61), U$12.2
T11_3: U$11.P$39 (CH59), U$12.3
T11_4: U$11.P$40 (CH57), U$12.4
T12_1: U$11.P$30 (CH56), U$12.8
T12_2: U$11.P$31 (CH58), U$12.7
T12_3: U$11.P$32 (CH60), U$12.6
T12_4: U$11.P$33 (CH62), U$12.5
T13_1: U$11.P$29 (CH54), U$12.9
T13_2: U$11.P$28 (CH52), U$12.10
T13_3: U$11.P$27 (CH50), U$12.11
T13_4: U$11.P$26 (CH48), U$12.12
T14_1: U$11.P$25 (CH46), U$12.13
T14_2: U$11.P$24 (CH44), U$12.14
T14_3: U$11.P$23 (CH42), U$12.15
T14_4: U$11.P$22 (CH40), U$12.16
T15_1: U$11.P$21 (CH38), U$12.17
T15_2: U$11.P$20 (CH36), U$12.18
T15_3: U$11.P$19 (CH34), U$12.19
T15_4: U$11.P$18 (CH32), U$12.20
T16_1: U$10.P$17 (CH30), U$12.21
T16_2: U$10.P$16 (CH28), U$12.22
T16_3: U$10.P$15 (CH26), U$12.23
T16_4: U$10.P$14 (CH24), U$12.24
T17_1: U$10.P$13 (CH22), U$12.25
T17_2: U$10.P$12 (CH20), U$12.26
T17_3: U$10.P$11 (CH18), U$12.27
T17_4: U$10.P$10 (CH16), U$12.28
T18_1: U$10.P$9 (CH14), U$12.29
T18_2: U$10.P$8 (CH12), U$12.30
T18_3: U$10.P$7 (CH10), U$12.31
T18_4: U$10.P$6 (CH8), U$12.32
T19_1: U$10.P$2 (CH0), U$12.36
T19_2: U$10.P$3 (CH2), U$12.35
T19_3: U$10.P$4 (CH4), U$12.34
T19_4: U$10.P$5 (CH6), U$12.33
T20_1: U$10.P$65 (CH7), U$12.37
T20_2: U$10.P$66 (CH5), U$12.38
T20_3: U$10.P$67 (CH3), U$12.39
T20_4: U$10.P$68 (CH1), U$12.40
T21_1: U$11.P$64 (CH9)
T21_2: U$11.P$63 (CH11)
T21_3: U$11.P$62 (CH13)
T21_4: U$11.P$61 (CH15)
T22_1: U$11.P$60 (CH17)
T22_2: U$11.P$59 (CH19)
T22_3: U$11.P$58 (CH21)
T22_4: U$11.P$57 (CH23)
T23_1: U$11.P$56 (CH25)
T23_2: U$11.P$55 (CH27)
T23_3: U$11.P$54 (CH29)
T23_4: U$11.P$53 (CH31)
T24_1: U$11.P$52 (CH33)
T24_2: U$11.P$51 (CH35)
T24_3: U$11.P$50 (CH37)
T24_4: U$11.P$49 (CH39)
T25_1: U$11.P$48 (CH41)
T25_2: U$11.P$47 (CH43)
T25_3: U$11.P$46 (CH45)
T25_4: U$11.P$45 (CH47)
T26_1: U$11.P$44 (CH49)
T26_2: U$11.P$43 (CH51)
T26_3: U$11.P$42 (CH53)
T26_4: U$11.P$41 (CH55)
T27_1: U$10.P$64 (CH9)
T27_2: U$10.P$63 (CH11)
T27_3: U$10.P$62 (CH13)
T27_4: U$10.P$61 (CH15)
T28_1: U$10.P$60 (CH17)
T28_2: U$10.P$59 (CH19)
T28_3: U$10.P$58 (CH21)
T28_4: U$10.P$57 (CH23)
T29_1: U$10.P$56 (CH25)
T29_2: U$10.P$55 (CH27)
T29_3: U$10.P$54 (CH29)
T29_4: U$10.P$53 (CH31)
T30_1: U$10.P$52 (CH33)
T30_2: U$10.P$51 (CH35)
T30_3: U$10.P$50 (CH37)
T30_4: U$10.P$49 (CH39)
T31_1: U$10.P$48 (CH41)
T31_2: U$10.P$47 (CH43)
T31_3: U$10.P$46 (CH45)
T31_4: U$10.P$45 (CH47)
T32_1: U$10.P$44 (CH49)
T32_2: U$10.P$43 (CH51)
T32_3: U$10.P$42 (CH53)
T32_4: U$10.P$41 (CH55)

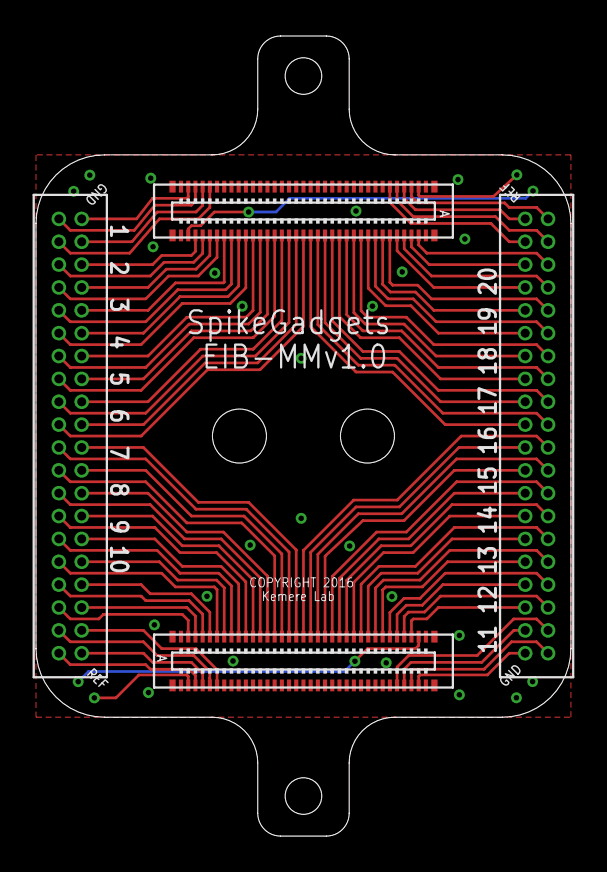
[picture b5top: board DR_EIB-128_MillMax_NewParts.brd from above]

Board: 2 copper layers, 29.7 x 44.5 mm, 12 parts (0 on the bottom side), 85 nets.

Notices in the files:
EIBs/Hirose128-Expanded/DR_EIB-128_expandedv1.3.brd:
COPYRIGHT 2014
EIBs/Hirose128-MillMax/DR_EIB-128_MillMax.brd:
COPYRIGHT 2015
EIBs/Hirose128-MillMax/DR_EIB-128_MillMax_NewParts.brd:
COPYRIGHT 2016
